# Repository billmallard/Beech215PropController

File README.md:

# Beechcraft Bonanza Electric Prop — Digital Governor Controller
### Open-Source Replacement for the Airborne Electronics 350A

> **A modern, proportional-control replacement for the Airborne Electronics 350A solid-state propeller governor — for Beechcraft Bonanza models with the Beech 215-210 electric prop.**

---

## The Problem This Solves

The original Airborne Electronics 350A (covered under STC SA2700WE) uses a **bang-bang control architecture** — the prop motor runs at full voltage until the RPM crosses the target, then reverses. This causes constant RPM hunting, which is made worse by:

- Freshly overhauled prop motors with more torque than the 50-year-old electronics expected
- Aging capacitors and resistors in the original controller that shrink the deadband
- The original panel rheostat giving no indication of what RPM is actually set
- Rough magneto signal from high-time mags degrading the RPM sensing

**This project replaces only the electronics inside the governor box.** The 7-pin Cannon connector, airframe wiring, prop motor, limit switches, and relays are all unchanged. From the aircraft's perspective, the interface is identical to the original.

## What It Does Differently

| Feature | Original 350A | This Controller |
|---|---|---|
| Control type | Bang-bang (full voltage on/off) | Proportional — slows motor near setpoint |
| Deadband | Fixed by aging analog components | Software-configurable (default ±25 RPM) |
| RPM display | None — knob position only | OLED shows set RPM and actual RPM |
| Presets | None | 5 named presets (Max, Cruise Climb, Cruise, Economy, Emergency) |
| Setpoint transition | Instant jump (causes full-duty relay surge) | Soft ramp 100 RPM/sec — smooth, no lurch |
| Fail-safe | RPM signal loss → no action | Loss of mag signal → relays de-energize, alarm displayed |
| Watchdog | None | Hardware watchdog resets MCU in 250ms if firmware stalls |
| Motor runaway protection | Limit switches only | 8-second relay timeout regardless of limit switch state |

## Who This Is For

Any Beechcraft Bonanza (straight 35 through G35, A35–G35) equipped with:
- The Beech 215-210 electric prop
- An existing Airborne Electronics 350A installation (STC SA2700WE)

If you have the stock mechanical governor, this is not applicable.

---

## Regulatory Note

This project is designed for **owner-produced parts** under 14 CFR Part 21.303. The STC SA2700WE defines the system by its external interface — the 7-pin connector, wire assignments, and functional behavior — all of which are preserved exactly. The electronics inside the governor housing are replaced. **This is a major alteration and requires FAA Form 337 approval signed by an IA.** See [docs/REGULATORY.md](docs/REGULATORY.md) for a detailed discussion and suggested 337 language.

---

## Hardware Overview

The system consists of two units:

**Governor Box** (replaces the 350A housing, mounts in the same location):
- Arduino Nano (ATmega328P)
- 6N137 optocoupler (galvanic isolation of magneto P-lead)
- ULN2003A Darlington array (relay driver)
- LM2596S-5V DC-DC switching regulator
- Supporting passives

**Panel Unit** (replaces the knob/rheostat assembly):
- SSD1306 1.3" OLED display (128×64, I2C)
- 5-position rotary switch (one detent per preset — Lorlin CK1024 or Grayhill 56-series)
- Original prop control knob reuses directly on the switch shaft

The PCB is a 100mm × 80mm 2-layer FR4 board, designed for JLCPCB fabrication at approximately **$2 for 5 boards**. The panel cable is 10 conductors (simplified from earlier designs).

---

## Repository Structure

```
bonanza-prop-governor/
├── README.md                    ← You are here
├── docs/
│   ├── ASSEMBLY.md              ← Step-by-step build instructions
│   ├── BENCH_TEST.md            ← Ground test procedure before aircraft installation
│   ├── WIRING.md                ← Connector pinout and wiring reference
│   ├── REGULATORY.md            ← FAA owner-produced parts guidance, 337 language
│   └── TROUBLESHOOTING.md       ← Fault codes, common issues
├── firmware/
│   └── governor_350A/
│       ├── README.md            ← Flashing guide, serial console, unit tests
│       ├── governor_350A.ino    ← Arduino sketch (fully commented)
│       ├── platformio.ini       ← PlatformIO build config (AVR + native test)
│       └── test/                ← Unity unit tests (runs on desktop, no hardware)
└── hardware/
    ├── 350A_governor.kicad_pcb  ← KiCad PCB file (open in KiCad 7+)
    ├── 350A_governor_JLCPCB.zip ← Ready-to-upload Gerber package for JLCPCB
    └── BOM.md                   ← Bill of materials with part numbers and sources
```

---

## Quick Start

1. **Order the PCB** — Upload `hardware/350A_governor_JLCPCB.zip` to [jlcpcb.com](https://jlcpcb.com). Default settings (2-layer, FR4, 1.6mm, HASL, green) are fine.
2. **Order components** — See [hardware/BOM.md](hardware/BOM.md). Total ~$55–95 for a complete build.
3. **Assemble** — Follow [docs/ASSEMBLY.md](docs/ASSEMBLY.md). All through-hole components; no SMD soldering.
4. **Flash firmware** — See [firmware/governor_350A/README.md](firmware/governor_350A/README.md) for full instructions (Arduino IDE, PlatformIO, and CLI). Set `PULSES_PER_REV` for your engine before flashing.
5. **Bench test** — Build the test harness described in [docs/BENCH_TEST.md](docs/BENCH_TEST.md) and verify operation before touching the aircraft.
6. **Install** — Follow [docs/ASSEMBLY.md](docs/ASSEMBLY.md) aircraft installation section. Have your IA present.

---

## Engine Compatibility

Set `PULSES_PER_REV` in the firmware before flashing:

| Engine | Cylinders | PULSES_PER_REV |
|---|---|---|
| Continental IO-470 | 6 | 3 |
| Continental IO-520 | 6 | 3 |
| Continental E-185/E-225 | 6 | 3 |
| Lycoming O-435 | 6 | 3 |

All early Bonanzas use Continental 6-cylinder engines. `PULSES_PER_REV = 3` is correct for all of them.

---

## Contributing

This project is maintained by the Bonanza owner community. Pull requests welcome for:
- Firmware improvements (better control algorithms, additional safety checks)
- Documentation corrections
- Hardware revisions (alternative component footprints, panel unit PCB)
- Flight test data and tuning recommendations

Please open an issue before starting significant work so efforts aren't duplicated.

---

## Security

This repository uses layered secret-prevention controls. See [SECURITY.md](SECURITY.md) for the full policy including vulnerability reporting and incident response steps.

| Layer | Tool | Trigger |
|---|---|---|
| Local pre-commit | `tools/security/scan_secrets.py` | Every `git commit` (staged files) |
| CI — SAST | CodeQL (C/C++ + Python) | Push, PR, weekly |
| CI — Secret scan | Gitleaks | Push, PR, weekly (full history) |

**Quick setup after cloning:**
```
pip install pre-commit
pre-commit install
```

Recommended GitHub repository settings: enable **Secret scanning**, **Push protection**, and **Dependabot** (Settings → Security).

---

## License

MIT License. See LICENSE file. This hardware and firmware may be freely built, modified, and used for personal aircraft. Commercial reproduction or sale requires separate arrangement.

---

## Acknowledgments

Richard Keiter of Airborne Electronics, Healdsburg CA, designed the original 350A and made it repairable by owners. This project is built on his philosophy. The complete original documentation is preserved in [docs/original_350A/](docs/original_350A/) for reference.

---

*This project is not affiliated with Beechcraft, Textron Aviation, or Airborne Electronics. It is an independent owner-community project. Install only with appropriate FAA authorization.*

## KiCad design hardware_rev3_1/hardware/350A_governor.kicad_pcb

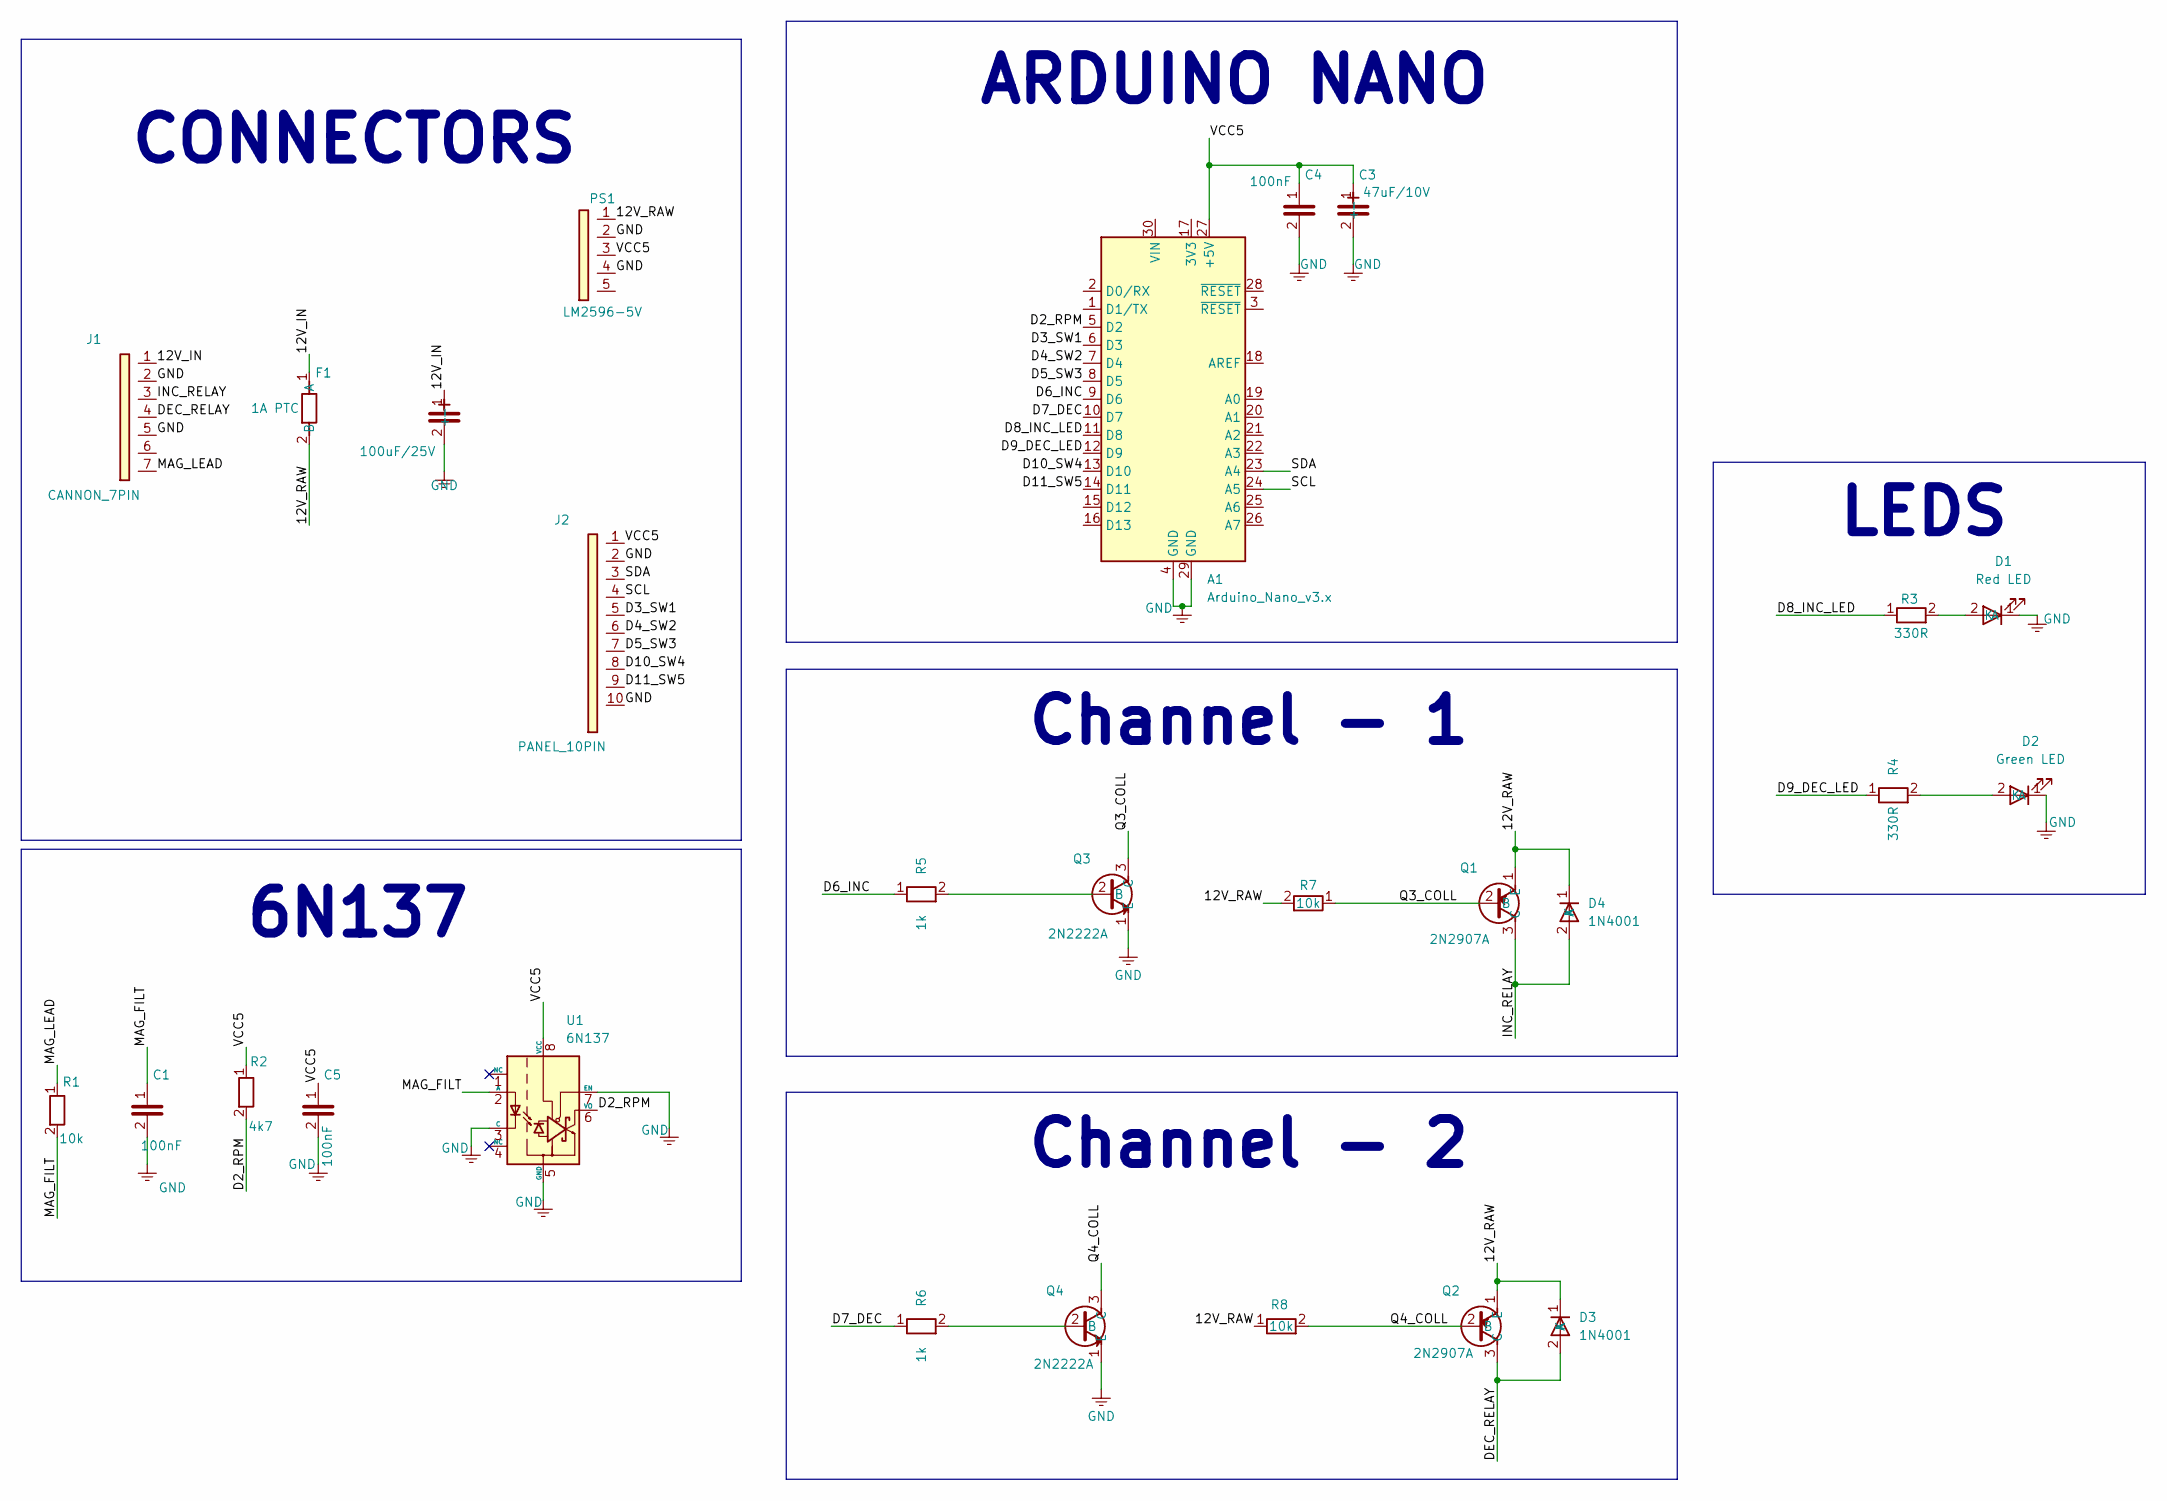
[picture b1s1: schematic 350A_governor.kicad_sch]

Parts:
A1: Arduino_Nano_v3.x; Arduino_Nano
C1, C4, C5: 100nF; C_Disc_D3.8mm_W2.6mm_P2.50mm
C2: 100uF/25V; CP_Radial_D5.0mm_P2.50mm
C3: 47uF/10V; CP_Radial_D8.0mm_P3.80mm
D1: Red LED
D2: Green LED
D3, D4: 1N4001; D_DO-41_SOD81_P10.16mm_Horizontal
F1: 1A PTC; Fuse_BelFuse_0ZRE0012FF_L8.3mm_W3.8mm
J1: CANNON_7PIN; PinHeader_1x07_P2.54mm_Vertical
J2: PANEL_10PIN; PinHeader_1x10_P2.54mm_Vertical
PS1: LM2596-5V; PinHeader_1x05_P2.54mm_Vertical
Q1, Q2: 2N2907A; TO-92L_Inline
Q3, Q4: 2N2222A; TO92254P470H750-3
R1, R7, R8: 10k; R_Axial_DIN0207_L6.3mm_D2.5mm_P7.62mm_Horizontal
R2: 4k7; R_Axial_DIN0207_L6.3mm_D2.5mm_P7.62mm_Horizontal
R3, R4: 330R; R_Axial_DIN0207_L6.3mm_D2.5mm_P7.62mm_Horizontal
R5, R6: 1k; R_Axial_DIN0207_L6.3mm_D2.5mm_P7.62mm_Horizontal
U1: 6N137; DIP-8_W7.62mm

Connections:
/12V_IN: C2.1 (+), F1.1 (A), J1.1
/12V_RAW: D3.1 (K), D4.1 (K), F1.2 (B), PS1.1, Q1.1 (E), Q2.1 (E), R7.2, R8.1
/D2_RPM: A1.5 (D2), R2.2, U1.6 (VO)
/D3_SW1: A1.6 (D3), J2.5
/D4_SW2: A1.7 (D4), J2.6
/D5_SW3: A1.8 (D5), J2.7
/D6_INC: A1.9 (D6), R5.1
/D7_DEC: A1.10 (D7), R6.1
/D8_INC_LED: A1.11 (D8), R3.1
/D9_DEC_LED: A1.12 (D9), R4.1
/D10_SW4: A1.13 (D10), J2.8
/D11_SW5: A1.14 (D11), J2.9
/DEC_RELAY: D3.2 (A), J1.4, Q2.3 (C)
/INC_RELAY: D4.2 (A), J1.3, Q1.3 (C)
/MAG_FILT: C1.1, R1.2, U1.2 (A)
/MAG_LEAD: J1.7, R1.1
/Q3_COLL: Q1.2 (B), Q3.3 (C), R7.1
/Q4_COLL: Q2.2 (B), Q4.3 (C), R8.2
/SCL: A1.24 (A5), J2.4
/SDA: A1.23 (A4), J2.3
/VCC5: A1.27 (+5V), C3.1 (+), C4.1, C5.1, J2.1, PS1.3, R2.1, U1.8 (VCC)
GND: A1.4 (GND), A1.29 (GND), C1.2, C2.2 (-), C3.2 (-), C4.2, C5.2, D1.1 (K), D2.1 (K), J1.2, J1.5, J2.2, J2.10, PS1.2, PS1.4, Q3.1 (E), Q4.1 (E), U1.3 (C), U1.5 (GND), U1.7 (EN)
unnamed: D1.2 (A), R3.2
unnamed: D2.2 (A), R4.2
unnamed: Q3.2 (B), R5.2
unnamed: Q4.2 (B), R6.2

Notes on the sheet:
ARDUINO NANO
Channel - 1
CONNECTORS
6N137
Channel - 2
LEDS

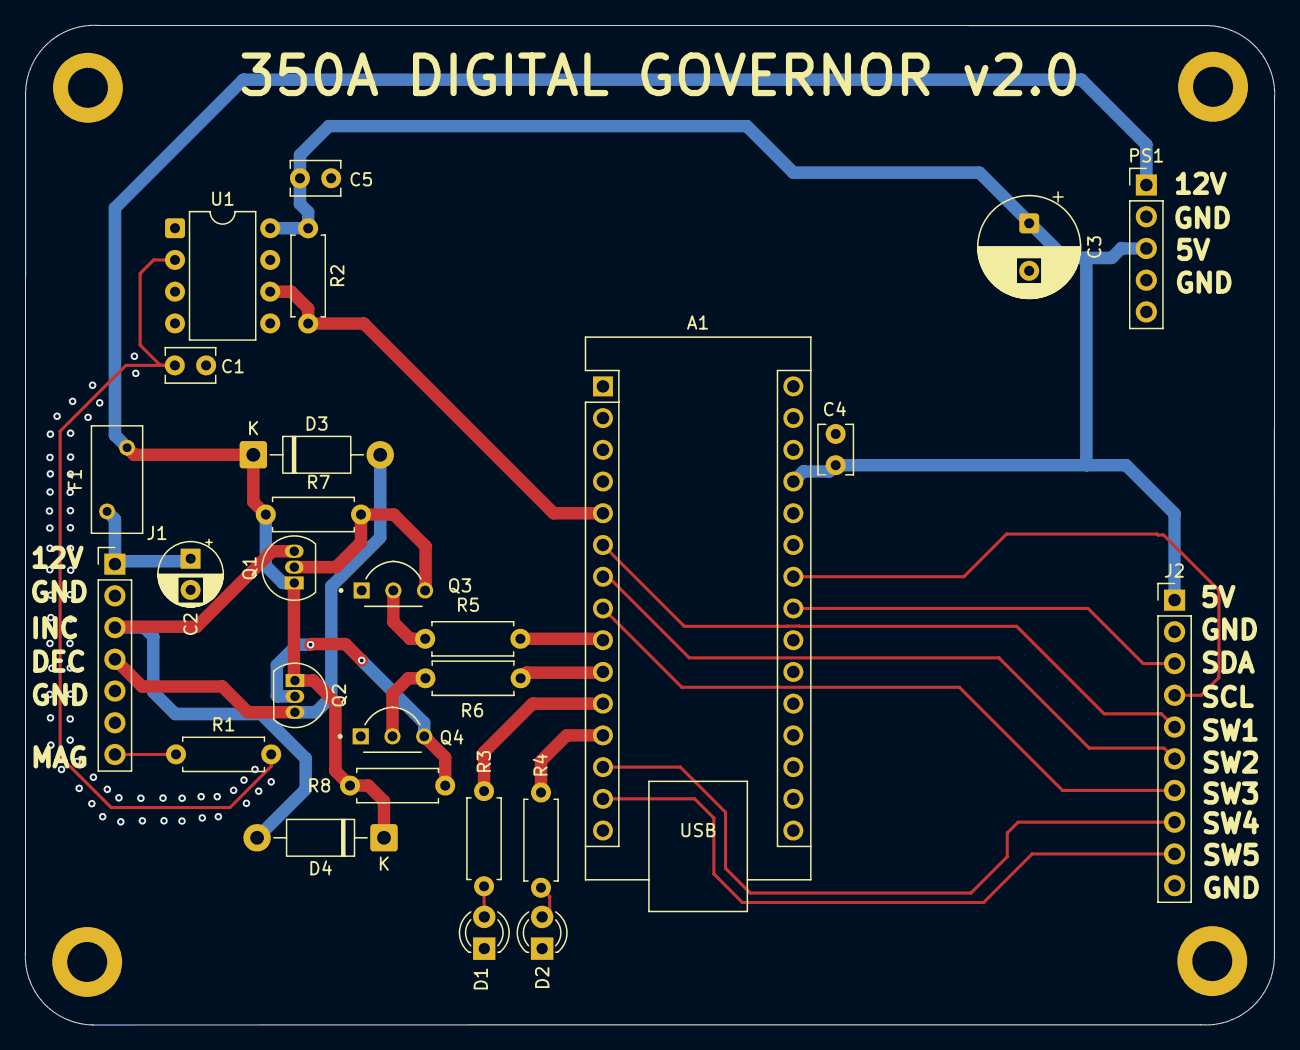
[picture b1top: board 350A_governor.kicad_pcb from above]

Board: 2 copper layers, 100.0 x 80.0 mm, 27 parts (0 on the bottom side), 26 nets.

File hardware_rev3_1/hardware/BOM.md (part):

# Bill of Materials — Rev 3

Complete parts list for one governor build. All parts available from Digi-Key, Mouser, or Amazon.
Links are to Digi-Key where possible — they're reliable, stock everything, and ship fast.

**Estimated total cost: $60–100** depending on sourcing (Amazon vs. Digi-Key, bulk vs. singles)

---

## PCB

| Item | Specification | Qty | Source | Est. Cost | Notes |
|---|---|---|---|---|---|
| Governor PCB | 100×80mm 2-layer FR4 | 5 | JLCPCB | ~$2 + shipping | Upload Gerber zip from `production/` folder; default settings; you get 5, use 1 |

**JLCPCB order settings:**
- Base Material: FR4
- Layers: 2
- PCB Thickness: 1.6mm
- Surface Finish: HASL (with lead) — cheapest and fine for this application
- Copper Weight: 1oz
- Everything else: defaults

---

## ICs and Active Components

| Ref | Part | Description | Digi-Key PN | Qty | Est. Cost | Notes |
|---|---|---|---|---|---|---|
| A1 | Arduino Nano (ATmega328P) | Microcontroller | — | 1 | $4–8 | Buy the CH340 version (most common on Amazon/eBay). Avoid Nano Every — different pinout. |
| U1 | 6N137 | High-speed optocoupler | 516-2878-5-ND | 1 | $0.60 | DIP-8. Do not substitute 4N25/4N35 — too slow for mag pulses. |
| PS1 | LM2596S-5V Module | DC-DC 5V switching regulator | — | 1 | $1–3 | Pre-built module. **Must be labeled "5V" not adjustable.** Verify output before installing. Available on Amazon, 10-packs for $8. |
| OLED | SSD1306 1.3" OLED | I2C display 128×64 | — | 1 | $6–10 | Must be I2C (2-wire), 128×64. Many on Amazon. Verify module is 4-pin (VCC/GND/SCL/SDA). |

---

## Transistors — High-Side Relay Driver

Two-channel NPN+PNP circuit replacing the ULN2003A from Rev 2. All TO-92 package.

| Ref | Part | Type | Digi-Key PN | Qty | Est. Cost | Notes |
|---|---|---|---|---|---|---|
| Q1, Q2 | 2N2907A | PNP — high-side switch | 2N2907A-ND | 2 | ~$0.50 ea | TO-92L. Switches +12V to relay coil. |
| Q3, Q4 | 2N2222A | NPN — level shifter | 2N2222A-ND | 2 | ~$0.30 ea | TO-92. Driven by Nano 5V logic. |

---

## Passives — Resistors

All resistors: 1/4W metal film, 1% tolerance

| Ref | Value | Digi-Key PN | Qty | Notes |
|---|---|---|---|---|
| R1 | 10kΩ | 10KEBK-ND | 1 | Magneto input current limit |
| R2 | 4.7kΩ | 4.7KEBK-ND | 1 | Optocoupler pull-up |
| R3, R4 | 330Ω | 330EBK-ND | 2 | LED current limiters |
| R5, R6 | 1kΩ | 1.0KEBK-ND | 2 | NPN base resistors (Q3, Q4) |
| R7, R8 | 10kΩ | 10KEBK-ND | 2 | PNP base pull-up to +12V (Q1, Q2) |

**Tip:** R1, R7, R8 are all 10kΩ — order 4 total on a single line item.

---

## Passives — Capacitors

| Ref | Value | Type | Digi-Key PN | Qty | Notes |
|---|---|---|---|---|---|
| C1, C4, C5 | 100nF (0.1µF) | Ceramic disc | 445-173-ND | 3 | Non-polarized; marked "104" |
| C2 | 100µF 25V | Electrolytic | 493-1215-ND | 1 | **POLARIZED** — observe polarity. 12V input bulk cap. |
| C3 | 47µF 10V | Electrolytic | 493-1205-ND | 1 | **POLARIZED** — observe polarity. 5V output filter cap. |

---

## Protection — Diodes and Fuse

| Ref | Part | Digi-Key PN | Qty | Notes |
|---|---|---|---|---|
| D3, D4 | 1N4001 | 1N4001FSCT-ND | 2 | Flyback diodes — clamp relay coil inductive spike when PNP switches off. **Do not omit.** Observe polarity (cathode to +12V). |
| F1 | 1A PTC resettable fuse | — | 1 | In series with +12V_RAW input. Self-resets after overcurrent. Belkin/Bel Fuse 0ZRE or equivalent. |

---

## Indicators

| Ref | Part | Digi-Key PN | Qty | Notes |
|---|---|---|---|---|
| D1 | 3mm Red LED | 754-1264-ND | 1 | Standard brightness; INC indicator |
| D2 | 3mm Green LED | 754-1221-ND | 1 | Standard brightness; DEC indicator |

---

## Connectors and Sockets

| Ref | Part | Qty | Notes |
|---|---|---|---|
| — | DIP-8 socket | 1 | For U1 (6N137). Use machined-pin (turned-pin) type for reliability. |
| — | 15-pin female single-row socket strip | 2 | For Arduino Nano. Cut to length or buy pre-cut Nano socket kit. |
| J1 | 1×7 2.54mm male header | 1 | 7-pin aircraft interface connector; or cut from 40-pin strip |
| J2 | 1×10 2.54mm male header | 1 | 10-pin panel unit connector; or cut from 40-pin strip |
| PS1 | 1×5 2.54mm male header | 1 | 5-pin for LM2596 module |
| — | 40-pin 2.54mm male header strip | 1 | Break-apart; covers J1/J2/PS1 (22 pins needed) |

**Tip:** Buy a 40-pin break-apart header strip and a 40-pin female socket strip on Amazon (~$1 each). These cover all connector needs on the board.

---

## Panel Unit Components

| Part | Qty | Est. Cost | Notes |
|---|---|---|---|
| 5-position rotary switch | 1 | $8–15 | **Single-pole, 5-position.** Lorlin CK1024 or Grayhill 56-series. Must have positive detents (not a continuous encoder). Panel-mount with standard ¼" shaft. |
| Project enclosure or panel plate | 1 | $5–15 | Size depends on your panel opening. Aluminum preferred. |
| Multi-conductor shielded cable | ~3 ft | $5–10 | 10 conductors sufficient. Belden 9536 or equivalent avionics-grade cable. |

**Switch selection notes:**
- Lorlin CK1024: 12-position base type, order 5-position variant. Available Mouser/Digi-Key. ~$8.
- Grayhill 56-series: industry-standard panel switch, very positive detent feel, standard ¼" D-shaft. ~$12–15.
- Avoid: continuous rotary encoders (no detents), wafer switches without detents, or switches with more than 5 positions (firmware only uses 5).
- The original prop control knob reuses directly on any ¼" D-shaft switch.

---

## Aircraft Interface

| Part | Qty | Source | Notes |
|---|---|---|---|
| 7-pin Cannon/MS connector (plug) | 1 | Aircraft Spruce, B&C Specialty, Stein Air | MS3106A-16-10S or equivalent. Match to existing connector on airframe. **Measure yours first.** ~$15–40 |
| Backshell for connector | 1 | Same sources | Strain relief; important for vibration environment |
| 22 AWG shielded wire | ~2 ft | Aircraft Spruce or local | For magneto lead connection inside governor box |
| Heat shrink tubing assortment | 1 | — | Cover all solder connections |
| Aluminum project box | 1 | Hammond Mfg or similar | Size your own governor box; original dimensions ~85×65×30mm |

---

## Tools Required (not included in cost estimate)

- Temperature-controlled soldering iron
- Multimeter
- Flush cutters
- Arduino IDE (free download)
- USB-A cable for programming Nano
- Oscilloscope (recommended but optional)
- Second Arduino Nano for bench test pulse generator (~$5 extra)

---

## Complete Order Summary

### Digi-Key single order (all board passives + ICs):
6N137 × 1, 2N2907A × 2, 2N2222A × 2, 1N4001 × 2, 10kΩ resistor × 4 (R1/R7/R8 + spare), 4.7kΩ × 1, 1kΩ × 2, 330Ω × 2, 100nF cap × 3, 100µF 25V cap × 1, 47µF 10V cap × 1, DIP-8 socket × 1

**Estimated Digi-Key subtotal: ~$14–20**

### Amazon or eBay (modules and panels):
Arduino Nano × 1, LM2596-5V module × 1, SSD1306 OLED 1.3" × 1, LED assortment (red + green 3mm) × 1, pin header strips × 1, female socket strips × 1, 1A PTC fuse × 1

**Estimated Amazon subtotal: ~$18–28**

### Mouser or Digi-Key (rotary switch):
5-position rotary switch (Lorlin CK1024 or Grayhill 56-series) × 1

**Estimated switch cost: ~$8–15**

### Aircraft Spruce or B&C (aircraft hardware):
7-pin Cannon connector and backshell, avionics wire

**Estimated aircraft hardware: ~$20–45**

### JLCPCB:
5× PCBs + shipping (typically $2 boards + $8–15 shipping to US)

**Estimated PCB: ~$10–17**

---

## Notes on Substitutions

**Arduino Nano:** The CH340 USB chip version is fine. Avoid:
- Arduino Nano Every (different pinout)
- Arduino Nano 33 IoT / BLE (3.3V logic — relay drive levels won't work)
- Any 3.3V variant

**6N137 optocoupler:** Do not substitute with slower optocouplers (4N25, 4N35, PC817). The magneto signal at cruise RPM is ~130 Hz and the pulse width matters. The 6N137 has 10ns response time — slower types will miss pulses or distort the signal.

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
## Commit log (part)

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2026-03-09 Updated engine pulse table
2026-03-09 File cleanup
2026-03-09 Reorg files
2026-03-09 Change in switch architecture
2026-03-09 Readme cleanup
2026-03-12 Fiverr design.
2026-03-12 Latest spec document
2026-03-13 Project cleanup
2026-04-11 Updated BOM with shopping lists
2026-04-12 Secret detection
2026-04-12 Build changes
2026-04-14 PCB Revisions after changes suggested
2026-04-20 Latest PCB version
2026-04-27 Rev 3 Hardware Delivery and name changes
2026-04-27 Rev 3_1 PCB and project lcleanup
2026-04-27 Build cleanup
2026-04-27 More cleanup
2026-04-27 Updated schematic
2026-04-27 Cleanup and .gitignore changes
2026-04-27 Deleting more stale files
2026-04-27 Updating documentation.
